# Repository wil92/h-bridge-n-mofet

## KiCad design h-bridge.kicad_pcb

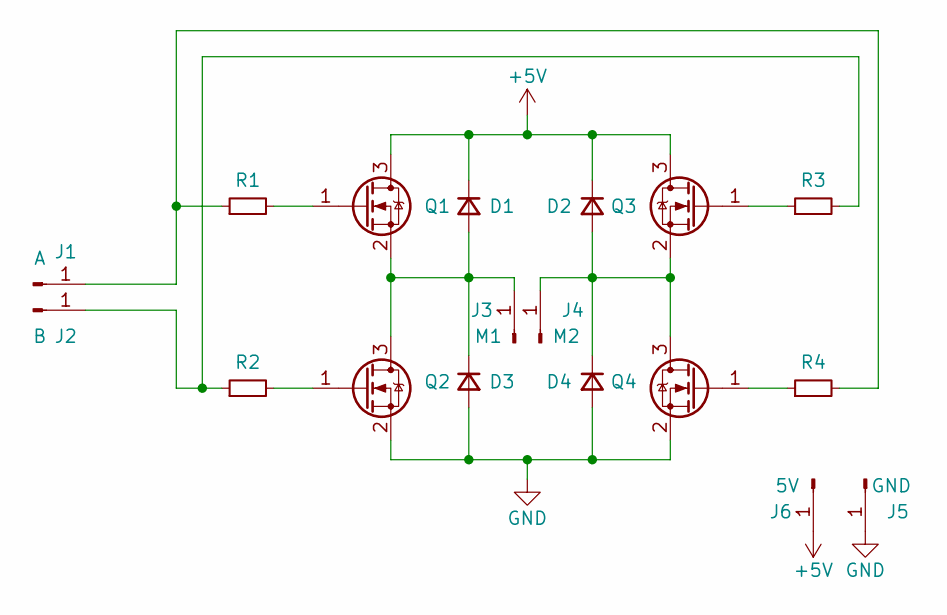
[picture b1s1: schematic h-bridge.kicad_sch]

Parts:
D1, D2, D3, D4: D_Small; D_SOD-323
J1: A; PinHeader_1x01_P2.00mm_Vertical
J2: B; PinHeader_1x01_P2.00mm_Vertical
J3: M1; PinHeader_1x01_P2.00mm_Vertical
J4: M2; PinHeader_1x01_P2.00mm_Vertical
J5: GND; PinHeader_1x01_P2.00mm_Vertical
J6: 5V; PinHeader_1x01_P2.00mm_Vertical
Q1, Q2, Q3, Q4: AO3400A; SOT-23
R1, R2, R3, R4: R_Small; R_0805_2012Metric

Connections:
+5V: D1.1 (K), D2.1 (K), J6.1, Q1.3 (D), Q3.3 (D)
GND: D3.2 (A), D4.2 (A), J5.1, Q2.2 (S), Q4.2 (S)
unnamed: D1.2 (A), D3.1 (K), J3.1, Q1.2 (S), Q2.3 (D)
unnamed: D2.2 (A), D4.1 (K), J4.1, Q3.2 (S), Q4.3 (D)
unnamed: J1.1, R1.1, R4.2
unnamed: J2.1, R2.1, R3.2
unnamed: Q1.1 (G), R1.2
unnamed: Q2.1 (G), R2.2
unnamed: Q3.1 (G), R3.1
unnamed: Q4.1 (G), R4.1

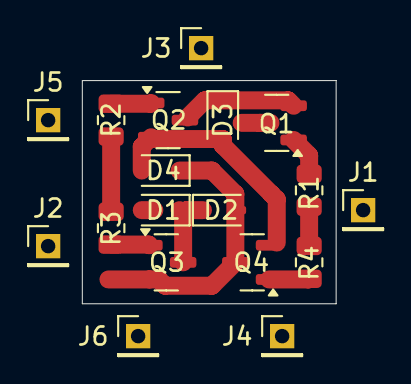
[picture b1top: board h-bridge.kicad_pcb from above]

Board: 2 copper layers, 14.1 x 12.4 mm, 18 parts (0 on the bottom side), 10 nets.

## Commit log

2026-03-18 last version
